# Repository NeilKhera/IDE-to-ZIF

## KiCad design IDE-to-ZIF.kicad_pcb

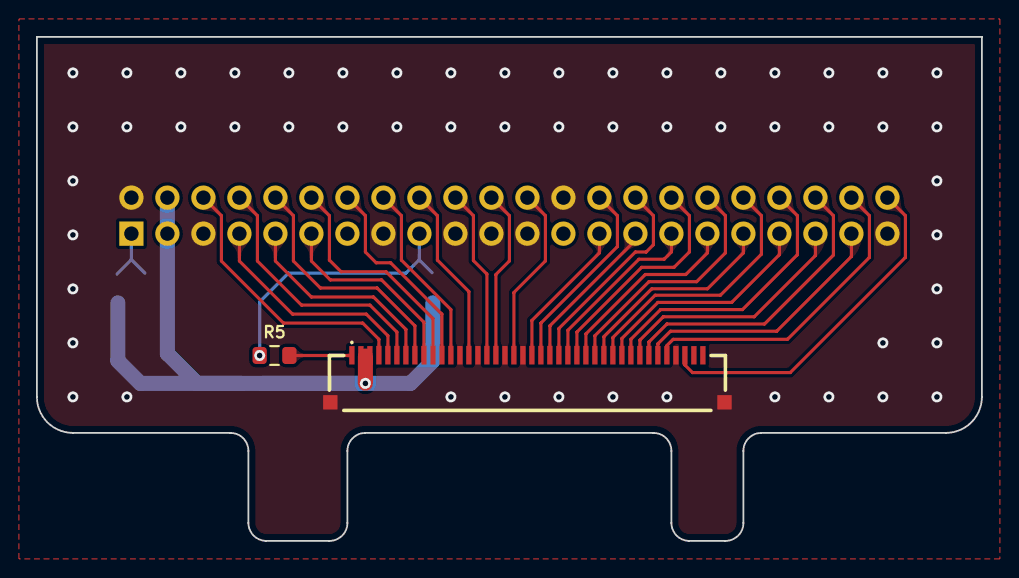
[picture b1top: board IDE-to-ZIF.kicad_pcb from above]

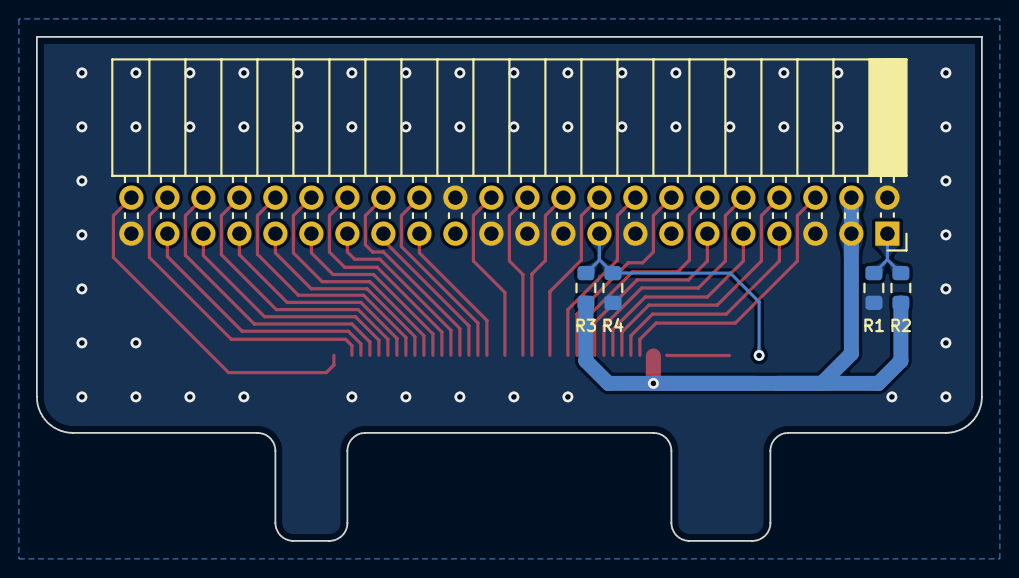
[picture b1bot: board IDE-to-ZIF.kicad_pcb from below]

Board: 2 copper layers, 52.5 x 28.0 mm, 7 parts (5 on the bottom side), 35 nets.

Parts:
J1: Conn_02x22_Odd_Even; PinSocket_2x22_P2.00mm_Horizontal
J2: F3311A7H121040E200
R1, R4, R5: 0; R_0603_1608Metric
R2, R3: DNF; R_0603_1608Metric

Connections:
+3.3V: J1.3, J1.4, J2.2, J2.3, R2.2, R3.2
/CS0: J1.8, J2.6
/CS1: J1.7, J2.5
/CSEL: J1.17, R3.1, R4.1, R5.1
/D00: J1.28, J2.22
/D01: J1.30, J2.24
/D02: J1.32, J2.26
/D03: J1.34, J2.28
/D04: J1.36, J2.30
/D05: J1.38, J2.32
/D06: J1.40, J2.34
/D07: J1.42, J2.36
/D08: J1.41, J2.35
/D09: J1.39, J2.33
/D10: J1.37, J2.31
/D11: J1.35, J2.29
/D12: J1.33, J2.27
/D13: J1.31, J2.25
/D14: J1.29, J2.23
/D15: J1.27, J2.21
/DA0: J1.10, J2.8
/DA1: J1.12, J2.10
/DA2: J1.9, J2.7
/DASP: J1.6, J2.4
/DEVADR: J2.1, R5.2
/DIOR: J1.20, J2.16
/DIOW: J1.22, J2.17
/DMACK: J1.16, J2.12
/DMARQ: J1.24, J2.19
/INTRQ: J1.14, J2.11
/IORDY: J1.18, J2.14
/PDIAG: J1.11, J2.9
/RESET: J1.44, J2.38
/TYPE: J1.1, R1.1, R2.1
GND: J1.2, J1.5, J1.15, J1.19, J1.21, J1.23, J1.26, J1.43, J2.13, J2.15, J2.18, J2.20, J2.37, J2.MP (MountPin), R1.2, R4.2

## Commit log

2024-05-03 Added .gitignore
2024-05-03 File upload
2024-05-03 Update to KiCad 8
